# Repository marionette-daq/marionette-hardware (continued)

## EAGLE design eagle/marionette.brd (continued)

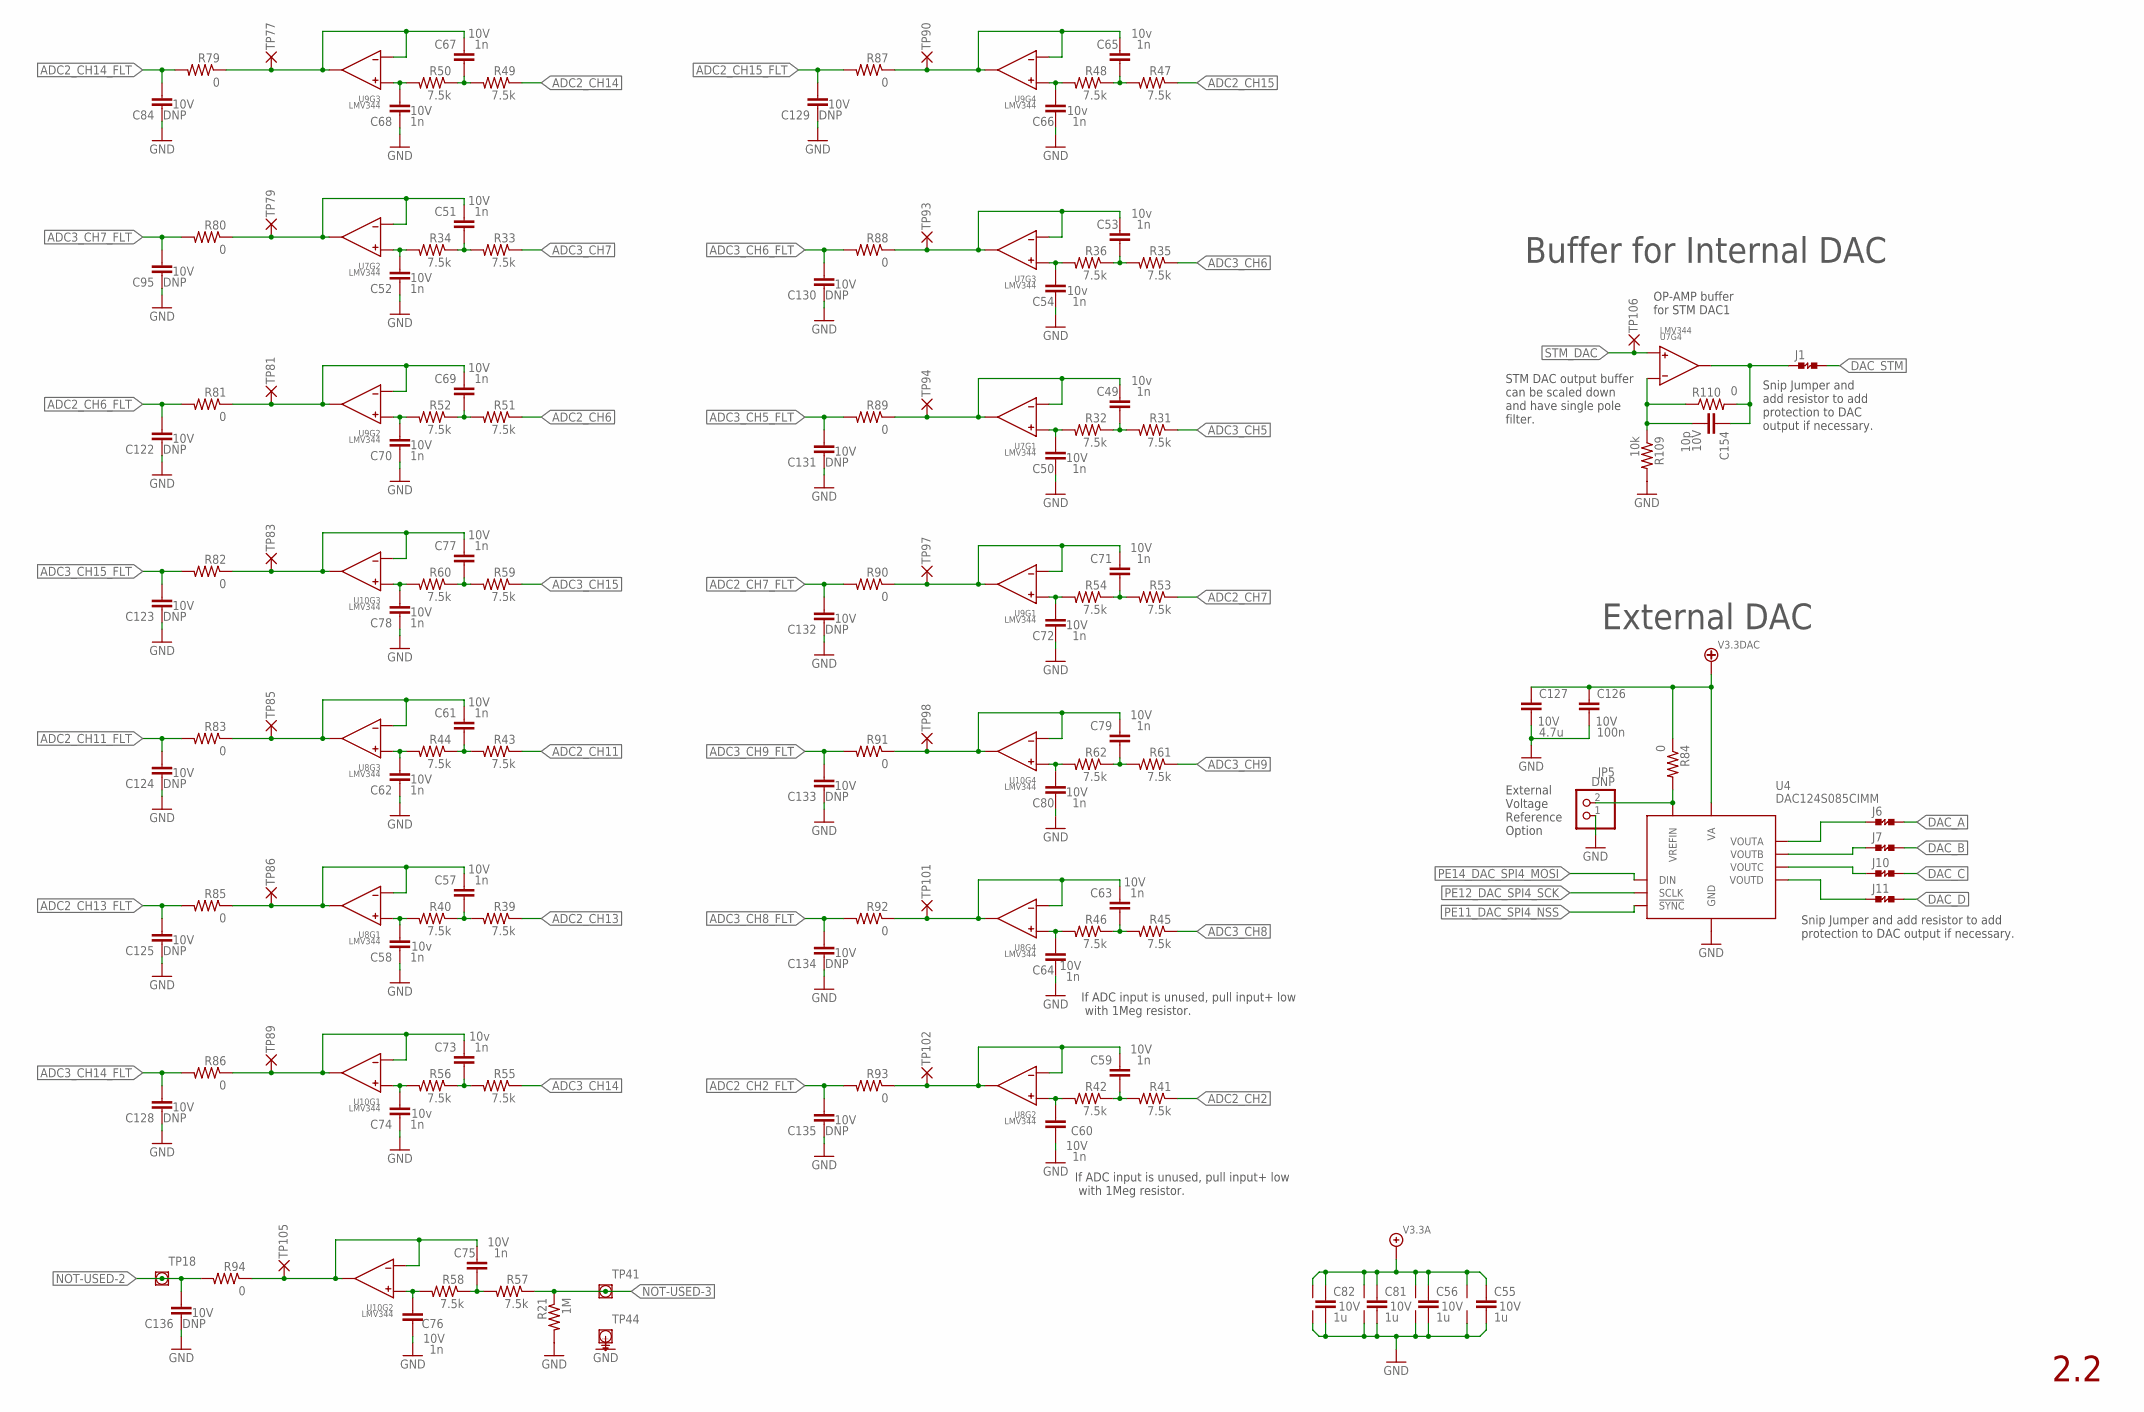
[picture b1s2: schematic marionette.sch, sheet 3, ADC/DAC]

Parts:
C49, C50, C51, C52, C53, C54, C57, C58, C59, C60, C61, C62, C63, C64, C65, C66, C67, C68, C69, C70, C71, C72, C73, C74, C75, C76, C77, C78, C79, C80: 1n; .0402-B
C55, C56, C81, C82: 1u; .0402-B
C84, C95, C122, C123, C124, C125, C128, C129, C130, C131, C132, C133, C134, C135, C136: DNP; .0402-B
C126: 100n; .0402-B
C127: 4.7u; .0805-B
C154: 10p; .0402-B
J1, J6, J7, J10, J11: JUMPER-SHORTED-CUTTABLE-E0402-0.3MM
JP5: DNP; 1X02
R21: 1M; .0402-B
R31, R32, R33, R34, R35, R36, R39, R40, R41, R42, R43, R44, R45, R46, R47, R48, R49, R50, R51, R52, R53, R54, R55, R56, R57, R58, R59, R60, R61, R62: 7.5k; .0402-B
R79, R80, R81, R82, R83, R84, R85, R86, R87, R88, R89, R90, R91, R92, R93, R94, R110: 0; .0402-B
R109: 10k; .0402-B
TP18, TP41: PAD+VIA_0.6MM
TP44: PAD+VIA_GND_0.6MM; PAD+GND_VIA_0.6MM
TP77, TP79, TP81, TP83, TP85, TP86, TP89, TP90, TP93, TP94, TP97, TP98, TP101, TP102, TP105, TP106: PAD+X-0.7-NO_CREAM+SILK; PAD-ROUND-0.7-NOCREAM+SILK
U4: DAC124S085CIMM; 10-TFSOP
U7, U8, U9, U10: LMV344; SOIC-14

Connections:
ADC1/2/3_CH2_OUT: C59.1, R93.1, TP102.PAD, U8.6 (-V), U8.7 (OUT)
ADC1/2/3_CH11_OUT: C61.1, R83.1, TP85.PAD, U8.8 (OUT), U8.9 (-V)
ADC1/2/3_CH13_OUT: C57.1, R85.1, TP86.PAD, U8.1 (OUT), U8.2 (-V)
ADC1/2/3_IN2+: C60.1, R42.2, U8.5 (+V)
ADC1/2/3_IN2_FILT: C59.2, R41.2, R42.1
ADC1/2/3_IN11+: C62.1, R44.2, U8.10 (+V)
ADC1/2/3_IN11_FILT: C61.2, R43.2, R44.1
ADC1/2/3_IN13+: C58.1, R40.2, U8.3 (+V)
ADC1/2/3_IN13_FILT: C57.2, R39.2, R40.1
ADC1/2_CH6_OUT: C69.1, R81.1, TP81.PAD, U9.6 (-V), U9.7 (OUT)
ADC1/2_CH7_OUT: C71.1, R90.1, TP97.PAD, U9.1 (OUT), U9.2 (-V)
ADC1/2_CH14_OUT: C67.1, R79.1, TP77.PAD, U9.8 (OUT), U9.9 (-V)
ADC1/2_CH15_OUT: C65.1, R87.1, TP90.PAD, U9.13 (-V), U9.14 (OUT)
ADC1/2_IN6+: C70.1, R52.2, U9.5 (+V)
ADC1/2_IN6_FILT: C69.2, R51.2, R52.1
ADC1/2_IN7+: C72.1, R54.2, U9.3 (+V)
ADC1/2_IN7_FILT: C71.2, R53.2, R54.1
ADC1/2_IN14+: C68.1, R50.2, U9.10 (+V)
ADC1/2_IN14_FILT: C67.2, R49.2, R50.1
ADC1/2_IN15+: C66.1, R48.2, U9.12 (+V)
ADC1/2_IN15_FILT: C65.2, R47.2, R48.1
ADC2_CH2: R41.1; also elsewhere on the board
ADC2_CH2_FLT: C135.1, R93.2; also elsewhere on the board
ADC2_CH6: R51.1; also elsewhere on the board
ADC2_CH6_FLT: C122.1, R81.2; also elsewhere on the board
ADC2_CH7: R53.1; also elsewhere on the board
ADC2_CH7_FLT: C132.1, R90.2; also elsewhere on the board
ADC2_CH11: R43.1; also elsewhere on the board
ADC2_CH11_FLT: C124.1, R83.2; also elsewhere on the board
ADC2_CH13: R39.1; also elsewhere on the board
ADC2_CH13_FLT: C125.1, R85.2; also elsewhere on the board
ADC2_CH14: R49.1; also elsewhere on the board
ADC2_CH14_FLT: C84.1, R79.2; also elsewhere on the board
ADC2_CH15: R47.1; also elsewhere on the board
ADC2_CH15_FLT: C129.1, R87.2; also elsewhere on the board
ADC3_CH4_OUT: C75.1, R94.1, TP105.PAD, U10.6 (-V), U10.7 (OUT)
ADC3_CH5: R31.1; also elsewhere on the board
ADC3_CH5_FLT: C131.1, R89.2; also elsewhere on the board
ADC3_CH5_OUT: C49.1, R89.1, TP94.PAD, U7.1 (OUT), U7.2 (-V)
ADC3_CH6: R35.1; also elsewhere on the board
ADC3_CH6_FLT: C130.1, R88.2; also elsewhere on the board
ADC3_CH6_OUT: C53.1, R88.1, TP93.PAD, U7.8 (OUT), U7.9 (-V)
ADC3_CH7: R33.1; also elsewhere on the board
ADC3_CH7_FLT: C95.1, R80.2; also elsewhere on the board
ADC3_CH7_OUT: C51.1, R80.1, TP79.PAD, U7.6 (-V), U7.7 (OUT)
ADC3_CH8: R45.1; also elsewhere on the board
ADC3_CH8_FLT: C134.1, R92.2; also elsewhere on the board
ADC3_CH8_OUT: C63.1, R92.1, TP101.PAD, U8.13 (-V), U8.14 (OUT)
ADC3_CH9: R61.1; also elsewhere on the board
ADC3_CH9_FLT: C133.1, R91.2; also elsewhere on the board
ADC3_CH14: R55.1; also elsewhere on the board
ADC3_CH14_FLT: C128.1, R86.2; also elsewhere on the board
ADC3_CH14_OUT: C73.1, R86.1, TP89.PAD, U10.1 (OUT), U10.2 (-V)
ADC3_CH15: R59.1; also elsewhere on the board
ADC3_CH15_FLT: C123.1, R82.2; also elsewhere on the board
ADC3_CH15_OUT: C77.1, R82.1, TP83.PAD, U10.8 (OUT), U10.9 (-V)
ADC3_IN4+: C76.1, R58.2, U10.5 (+V)
ADC3_IN4_FILT: C75.2, R57.2, R58.1
ADC3_IN5+: C50.1, R32.2, U7.3 (+V)
ADC3_IN5_FILT: C49.2, R31.2, R32.1
ADC3_IN6+: C54.1, R36.2, U7.10 (+V)
ADC3_IN6_FILT: C53.2, R35.2, R36.1
ADC3_IN7+: C52.1, R34.2, U7.5 (+V)
ADC3_IN7_FILT: C51.2, R33.2, R34.1
ADC3_IN8+: C64.1, R46.2, U8.12 (+V)
ADC3_IN8_FILT: C63.2, R45.2, R46.1
ADC3_IN9+: C80.1, R62.2, U10.12 (+V)
ADC3_IN9_FILT: C79.2, R61.2, R62.1
ADC3_IN9_OUT: C79.1, R91.1, TP98.PAD, U10.13 (-V), U10.14 (OUT)
ADC3_IN14+: C74.1, R56.2, U10.3 (+V)
ADC3_IN14_FILT: C73.2, R55.2, R56.1
ADC3_IN15+: C78.1, R60.2, U10.10 (+V)
ADC3_IN15_FILT: C77.2, R59.2, R60.1
DAC124_VREFIN: JP5.2, R84.2, U4.7 (VREFIN)
DAC_A: J6.2; also elsewhere on the board
DAC_A_JUMPERED: J6.1, U4.2 (VOUTA)
DAC_B: J7.2; also elsewhere on the board
DAC_B_JUMPERED: J7.1, U4.3 (VOUTB)
DAC_C: J10.2; also elsewhere on the board
DAC_C_JUMPERED: J10.1, U4.4 (VOUTC)
DAC_D: J11.2; also elsewhere on the board
DAC_D_JUMPERED: J11.1, U4.5 (VOUTD)
DAC_STM: J1.2; also elsewhere on the board
GND: C50.2, C52.2, C54.2, C55.2, C56.2, C58.2, C60.2, C62.2, C64.2, C66.2, C68.2, C70.2, C72.2, C74.2, C76.2, C78.2, C80.2, C81.2, C82.2, C84.2, C95.2, C122.2, C123.2, C124.2, C125.2, C126.2, C127.2, C128.2, C129.2, C130.2, C131.2, C132.2, C133.2, C134.2, C135.2, C136.2, JP5.1, R21.2, R109.2, TP44.TP, U4.6 (GND), U7.11 (GND), U8.11 (GND), U9.11 (GND), U10.11 (GND); also elsewhere on the board
NOT-USED-2: C136.1, R94.2, TP18.TP
NOT-USED-3: R21.1, R57.1, TP41.TP
PE11_DAC_SPI4_NSS: U4.9 (!SYNC!); also elsewhere on the board
PE12_DAC_SPI4_SCK: U4.10 (SCLK); also elsewhere on the board
PE14_DAC_SPI4_MOSI: U4.8 (DIN); also elsewhere on the board
STM_DAC: TP106.PAD, U7.12 (+V); also elsewhere on the board
STM_DAC-: C154.2, R109.1, R110.1, U7.13 (-V)
STM_DAC_OUT: C154.1, J1.1, R110.2, U7.14 (OUT)
V3.3A: C55.1, C56.1, C81.1, C82.1, U7.4 (VCC), U8.4 (VCC), U9.4 (VCC), U10.4 (VCC); also elsewhere on the board
V3.3DAC: C126.1, C127.1, R84.1, U4.1 (VA); also elsewhere on the board

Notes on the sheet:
OP-AMP buffer for STM DAC1
External DAC
Buffer for Internal DAC
External Voltage Reference Option
STM DAC output buffer can be scaled down and have single pole filter.
If ADC input is unused, pull input+ low with 1Meg resistor.
Snip Jumper and add resistor to add protection to DAC output if necessary.
Snip Jumper and add resistor to add protection to DAC output if necessary.

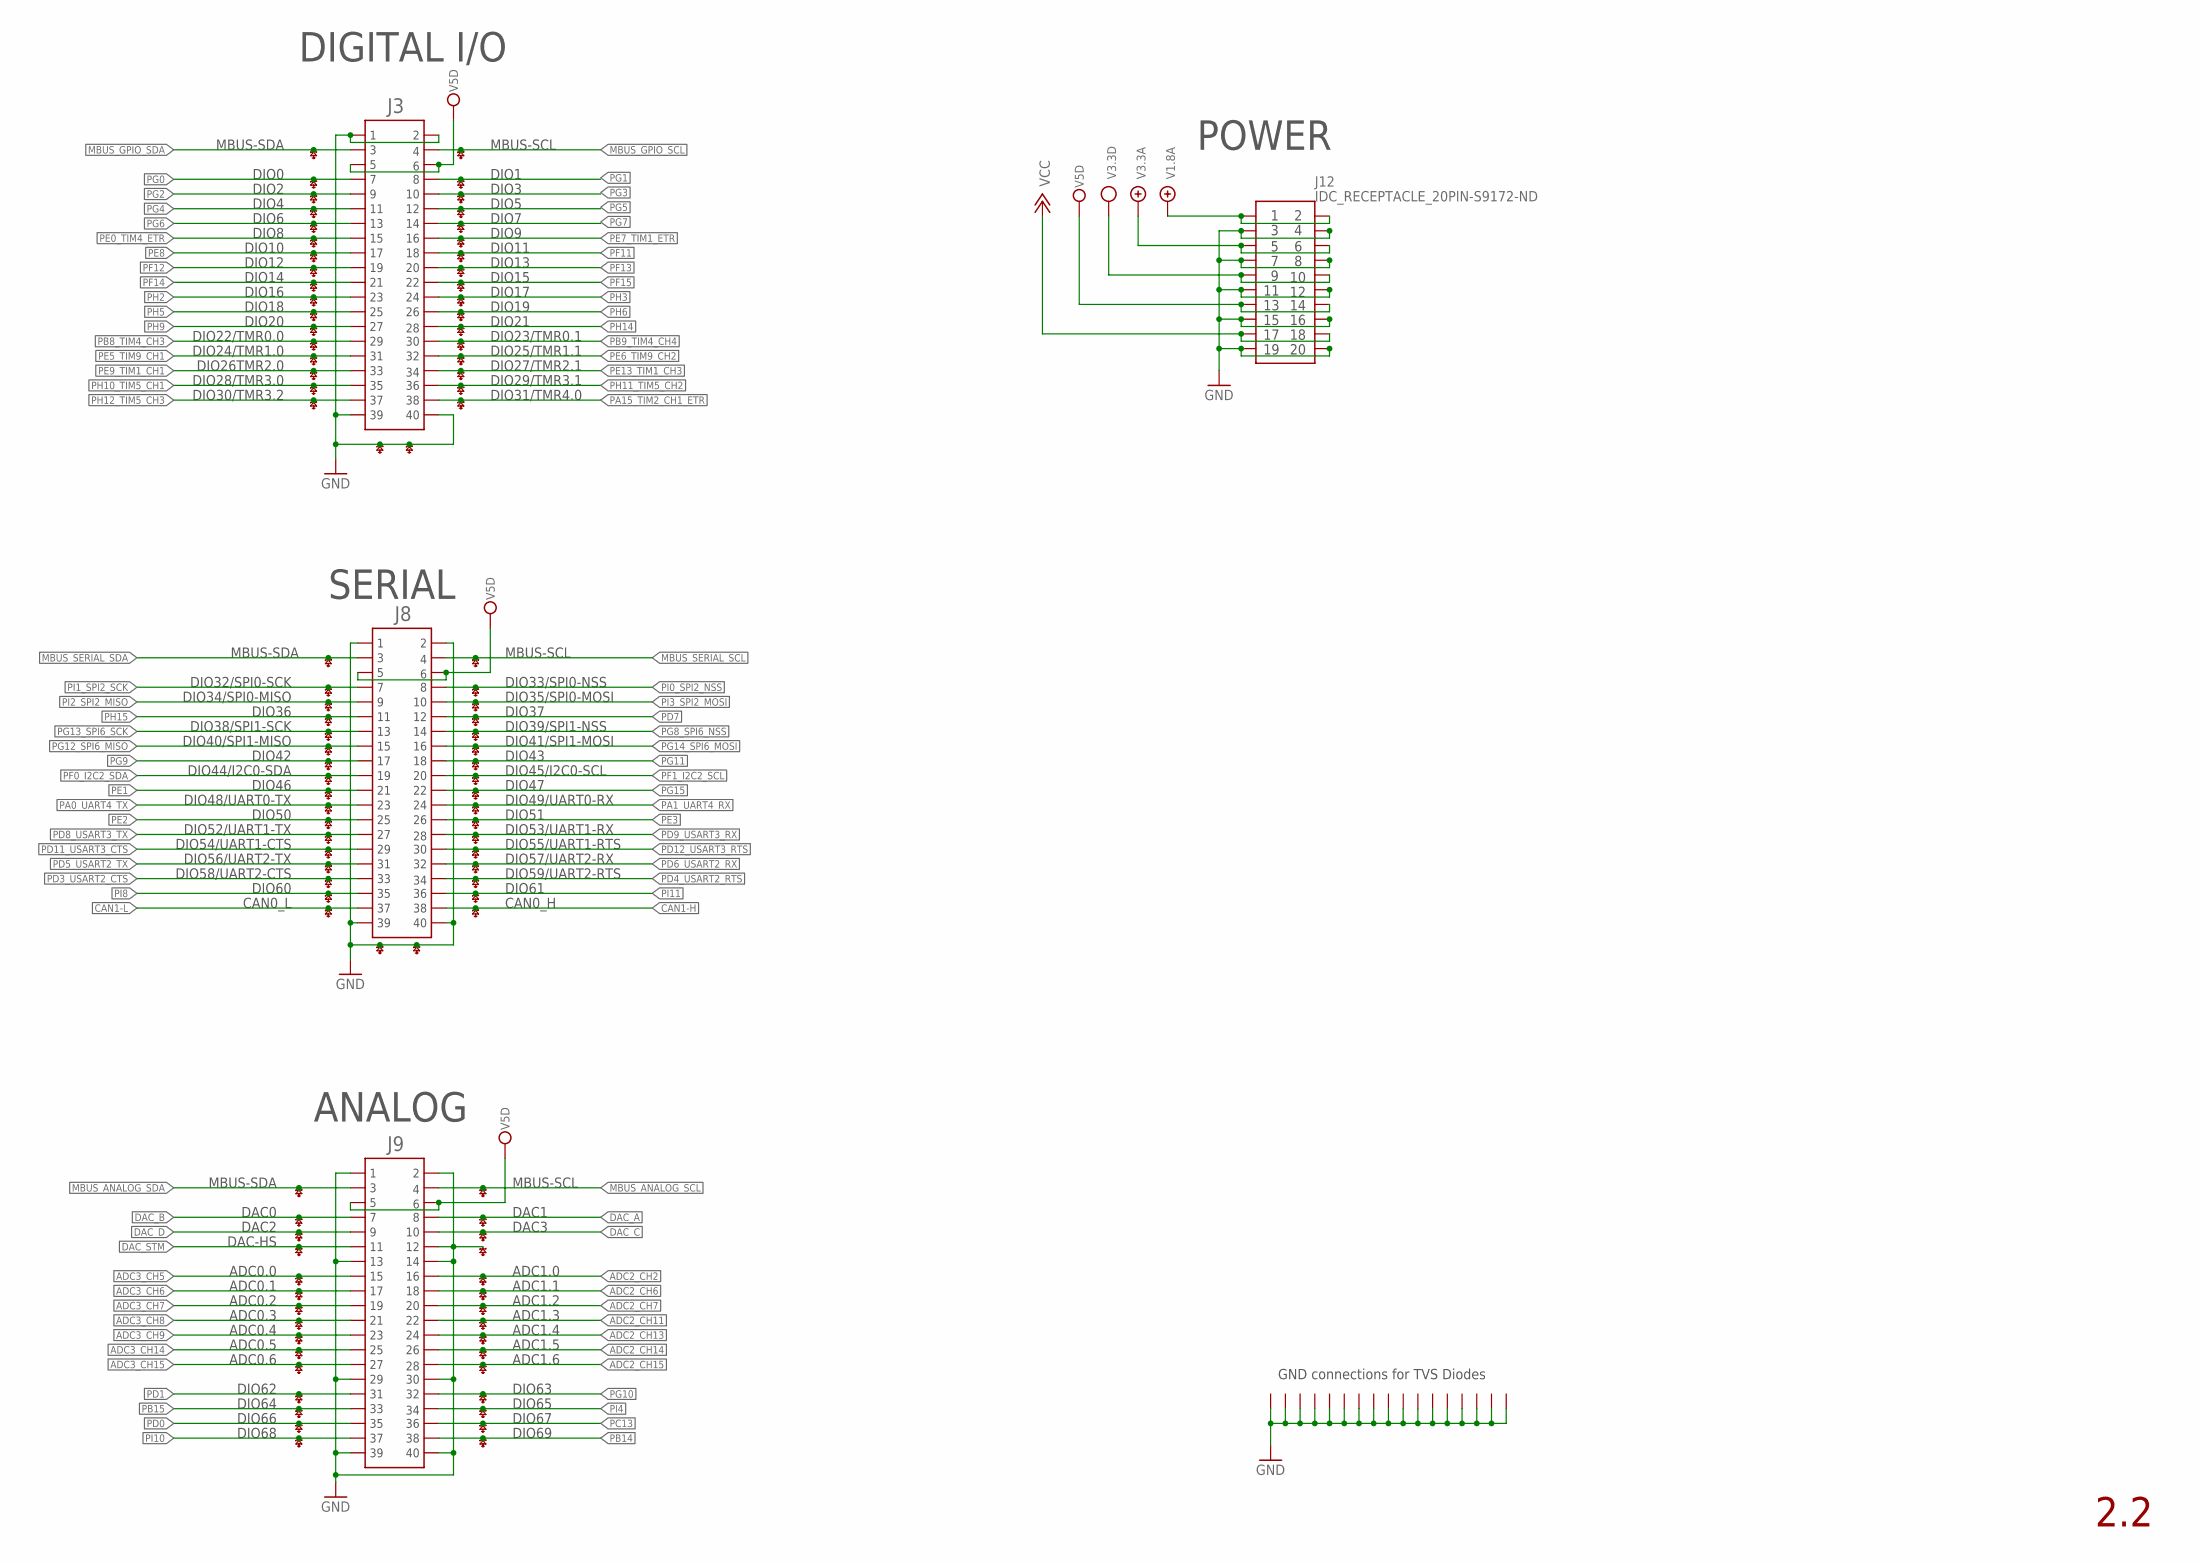
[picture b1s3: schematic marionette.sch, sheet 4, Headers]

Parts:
D1, D2, D4, D5, D6, D7, D8, D9, D10, D11, D12, D13, D14, D15, D16, D17, D18: ESD8006-ESD8006; UDFN-8-3.3X1.0_6MIL
J3, J8, J9: IDC_RECEPTACLE_2X20-S9175-ND; IDC_RECEPTACLES
J12: IDC_RECEPTACLE_20PIN-S9172-ND; IDC_RECEPTACLES_20PIN

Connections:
ADC2_CH2: D1.5 (CATHODE), J9.16; also elsewhere on the board
ADC2_CH6: D1.2 (CATHODE), J9.18; also elsewhere on the board
ADC2_CH7: D5.7 (CATHODE), J9.20; also elsewhere on the board
ADC2_CH11: D5.4 (CATHODE), J9.22; also elsewhere on the board
ADC2_CH13: D5.2 (CATHODE), J9.24; also elsewhere on the board
ADC2_CH14: D6.7 (CATHODE), J9.26; also elsewhere on the board
ADC2_CH15: D6.4 (CATHODE), J9.28; also elsewhere on the board
ADC3_CH5: D1.4 (CATHODE), J9.15; also elsewhere on the board
ADC3_CH6: D1.1 (CATHODE), J9.17; also elsewhere on the board
ADC3_CH7: D5.8 (CATHODE), J9.19; also elsewhere on the board
ADC3_CH8: D5.5 (CATHODE), J9.21; also elsewhere on the board
ADC3_CH9: D5.1 (CATHODE), J9.23; also elsewhere on the board
ADC3_CH14: D6.8 (CATHODE), J9.25; also elsewhere on the board
ADC3_CH15: D6.5 (CATHODE), J9.27; also elsewhere on the board
CAN1-H: D12.4 (CATHODE), J8.38; also elsewhere on the board
CAN1-L: D12.5 (CATHODE), J8.37; also elsewhere on the board
DAC_A: D2.5 (CATHODE), J9.8; also elsewhere on the board
DAC_B: D2.4 (CATHODE), J9.7; also elsewhere on the board
DAC_C: D2.2 (CATHODE), J9.10; also elsewhere on the board
DAC_D: D2.1 (CATHODE), J9.9; also elsewhere on the board
DAC_STM: D1.8 (CATHODE), J9.11; also elsewhere on the board
GND: D1.3 (PIN), D1.6 (PIN), D1.7 (CATHODE), D1.9 (PIN), D1.10 (PIN), D2.3 (PIN), D2.6 (PIN), D2.9 (PIN), D2.10 (PIN), D4.3 (PIN), D4.6 (PIN), D4.9 (PIN), D4.10 (PIN), D5.3 (PIN), D5.6 (PIN), D5.9 (PIN), D5.10 (PIN), D6.3 (PIN), D6.6 (PIN), D6.9 (PIN), D6.10 (PIN), D7.3 (PIN), D7.6 (PIN), D7.9 (PIN), D7.10 (PIN), D8.3 (PIN), D8.6 (PIN), D8.9 (PIN), D8.10 (PIN), D9.3 (PIN), D9.6 (PIN), D9.9 (PIN), D9.10 (PIN), D10.3 (PIN), D10.6 (PIN), D10.9 (PIN), D10.10 (PIN), D11.3 (PIN), D11.6 (PIN), D11.9 (PIN), D11.10 (PIN), D12.1 (CATHODE), D12.2 (CATHODE), D12.3 (PIN), D12.6 (PIN), D12.9 (PIN), D12.10 (PIN), D13.1 (CATHODE), D13.2 (CATHODE), D13.3 (PIN), D13.6 (PIN), D13.9 (PIN), D13.10 (PIN), D14.3 (PIN), D14.6 (PIN), D14.9 (PIN), D14.10 (PIN), D15.3 (PIN), D15.6 (PIN), D15.9 (PIN), D15.10 (PIN), D16.3 (PIN), D16.6 (PIN), D16.9 (PIN), D16.10 (PIN), D17.3 (PIN), D17.6 (PIN), D17.9 (PIN), D17.10 (PIN), D18.3 (PIN), D18.6 (PIN), D18.9 (PIN), D18.10 (PIN), J3.1, J3.2, J3.39, J3.40, J8.1, J8.2, J8.39, J8.40, J9.1, J9.2, J9.12, J9.13, J9.14, J9.29, J9.30, J9.39, J9.40, J12.3, J12.4, J12.7, J12.8, J12.11, J12.12, J12.15, J12.16, J12.19, J12.20; also elsewhere on the board
MBUS_ANALOG_SCL: D2.7 (CATHODE), J9.4; also elsewhere on the board
MBUS_ANALOG_SDA: D2.8 (CATHODE), J9.3; also elsewhere on the board
MBUS_GPIO_SCL: D18.8 (CATHODE), J3.4; also elsewhere on the board
MBUS_GPIO_SDA: D18.7 (CATHODE), J3.3; also elsewhere on the board
MBUS_SERIAL_SCL: D4.7 (CATHODE), J8.4; also elsewhere on the board
MBUS_SERIAL_SDA: D4.8 (CATHODE), J8.3; also elsewhere on the board
PA0_UART4_TX: D9.8 (CATHODE), J8.23; also elsewhere on the board
PA1_UART4_RX: D9.7 (CATHODE), J8.24; also elsewhere on the board
PA15_TIM2_CH1_ETR: D13.4 (CATHODE), J3.38; also elsewhere on the board
PB8_TIM4_CH3: D14.8 (CATHODE), J3.29; also elsewhere on the board
PB9_TIM4_CH4: D14.7 (CATHODE), J3.30; also elsewhere on the board
PB14: D7.2 (CATHODE), J9.38; also elsewhere on the board
PB15: D7.8 (CATHODE), J9.33; also elsewhere on the board
PC13: D7.4 (CATHODE), J9.36; also elsewhere on the board
PD0: D7.5 (CATHODE), J9.35; also elsewhere on the board
PD1: D6.1 (CATHODE), J9.31; also elsewhere on the board
PD3_USART2_CTS: D11.1 (CATHODE), J8.33; also elsewhere on the board
PD4_USART2_RTS: D11.2 (CATHODE), J8.34; also elsewhere on the board
PD5_USART2_TX: D11.5 (CATHODE), J8.31; also elsewhere on the board
PD6_USART2_RX: D11.4 (CATHODE), J8.32; also elsewhere on the board
PD7: D8.7 (CATHODE), J8.12; also elsewhere on the board
PD8_USART3_TX: D9.1 (CATHODE), J8.27; also elsewhere on the board
PD9_USART3_RX: D9.2 (CATHODE), J8.28; also elsewhere on the board
PD11_USART3_CTS: D11.8 (CATHODE), J8.29; also elsewhere on the board
PD12_USART3_RTS: D11.7 (CATHODE), J8.30; also elsewhere on the board
PE0_TIM4_ETR: D17.1 (CATHODE), J3.15; also elsewhere on the board
PE1: D10.1 (CATHODE), J8.21; also elsewhere on the board
PE2: D9.5 (CATHODE), J8.25; also elsewhere on the board
PE3: D9.4 (CATHODE), J8.26; also elsewhere on the board
PE5_TIM9_CH1: D14.5 (CATHODE), J3.31; also elsewhere on the board
PE6_TIM9_CH2: D14.4 (CATHODE), J3.32; also elsewhere on the board
PE7_TIM1_ETR: D17.2 (CATHODE), J3.16; also elsewhere on the board
PE8: D16.8 (CATHODE), J3.17; also elsewhere on the board
PE9_TIM1_CH1: D14.1 (CATHODE), J3.33; also elsewhere on the board
PE13_TIM1_CH3: D14.2 (CATHODE), J3.34; also elsewhere on the board
PF0_I2C2_SDA: D10.5 (CATHODE), J8.19; also elsewhere on the board
PF1_I2C2_SCL: D10.4 (CATHODE), J8.20; also elsewhere on the board
PF11: D16.7 (CATHODE), J3.18; also elsewhere on the board
PF12: D16.5 (CATHODE), J3.19; also elsewhere on the board
PF13: D16.4 (CATHODE), J3.20; also elsewhere on the board
PF14: D16.1 (CATHODE), J3.21; also elsewhere on the board
PF15: D16.2 (CATHODE), J3.22; also elsewhere on the board
PG0: D18.5 (CATHODE), J3.7; also elsewhere on the board
PG1: D18.4 (CATHODE), J3.8; also elsewhere on the board
PG2: D18.2 (CATHODE), J3.9; also elsewhere on the board
PG3: D18.1 (CATHODE), J3.10; also elsewhere on the board
PG4: D17.8 (CATHODE), J3.11; also elsewhere on the board
PG5: D17.7 (CATHODE), J3.12; also elsewhere on the board
PG6: D17.5 (CATHODE), J3.13; also elsewhere on the board
PG7: D17.4 (CATHODE), J3.14; also elsewhere on the board
PG8_SPI6_NSS: D8.4 (CATHODE), J8.14; also elsewhere on the board
PG9: D10.8 (CATHODE), J8.17; also elsewhere on the board
PG10: D6.2 (CATHODE), J9.32; also elsewhere on the board
PG11: D10.7 (CATHODE), J8.18; also elsewhere on the board
PG12_SPI6_MISO: D8.1 (CATHODE), J8.15; also elsewhere on the board
PG13_SPI6_SCK: D8.5 (CATHODE), J8.13; also elsewhere on the board
PG14_SPI6_MOSI: D8.2 (CATHODE), J8.16; also elsewhere on the board
PG15: D10.2 (CATHODE), J8.22; also elsewhere on the board
PH2: D15.8 (CATHODE), J3.23; also elsewhere on the board
PH3: D15.7 (CATHODE), J3.24; also elsewhere on the board
PH5: D15.5 (CATHODE), J3.25; also elsewhere on the board
PH6: D15.4 (CATHODE), J3.26; also elsewhere on the board
PH9: D15.1 (CATHODE), J3.27; also elsewhere on the board
PH10_TIM5_CH1: D13.8 (CATHODE), J3.35; also elsewhere on the board
PH11_TIM5_CH2: D13.7 (CATHODE), J3.36; also elsewhere on the board
PH12_TIM5_CH3: D13.5 (CATHODE), J3.37; also elsewhere on the board
PH14: D15.2 (CATHODE), J3.28; also elsewhere on the board
PH15: D8.8 (CATHODE), J8.11; also elsewhere on the board
PI0_SPI2_NSS: D4.5 (CATHODE), J8.8; also elsewhere on the board
PI1_SPI2_SCK: D4.4 (CATHODE), J8.7; also elsewhere on the board
PI2_SPI2_MISO: D4.1 (CATHODE), J8.9; also elsewhere on the board
PI3_SPI2_MOSI: D4.2 (CATHODE), J8.10; also elsewhere on the board
PI4: D7.7 (CATHODE), J9.34; also elsewhere on the board
PI8: D12.8 (CATHODE), J8.35; also elsewhere on the board
PI10: D7.1 (CATHODE), J9.37; also elsewhere on the board
PI11: D12.7 (CATHODE), J8.36; also elsewhere on the board
V1.8A: J12.1, J12.2; also elsewhere on the board
V3.3A: J12.5, J12.6; also elsewhere on the board
V3.3D: J12.9, J12.10; also elsewhere on the board
V5D: J3.5, J3.6, J8.5, J8.6, J9.5, J9.6, J12.13, J12.14; also elsewhere on the board
VCC: J12.17, J12.18; also elsewhere on the board

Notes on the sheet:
POWER
GND connections for TVS Diodes
DIO22/TMR0.0
DIO23/TMR0.1
DIO24/TMR1.0
DIO25/TMR1.1
DIO26TMR2.0
DIO27/TMR2.1
DIO28/TMR3.0
DIO29/TMR3.1
DIO30/TMR3.2
DIO31/TMR4.0
DAC0
DAC1
DAC2
DAC3
DAC-HS
ADC1.0
ADC1.1
ADC1.2
ADC1.3
ADC1.4
ADC1.5
ADC0.0
ADC0.1
ADC0.2
ADC0.3
ADC0.4
ADC0.5
DIO32/SPI0-SCK
DIO34/SPI0-MISO
DIO35/SPI0-MOSI
DIO33/SPI0-NSS
DIO38/SPI1-SCK
DIO40/SPI1-MISO
DIO41/SPI1-MOSI
DIO39/SPI1-NSS
DIO44/I2C0-SDA
DIO45/I2C0-SCL
CAN0_L

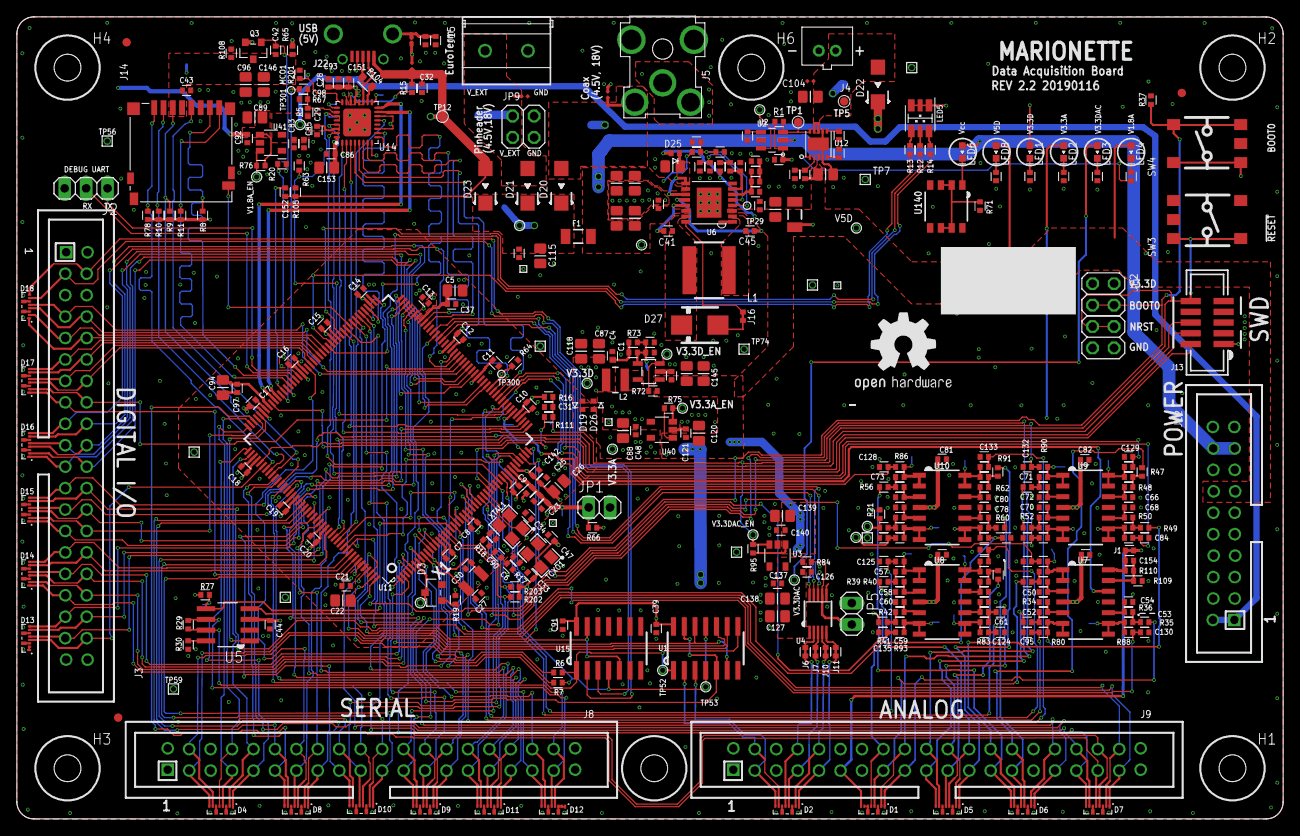
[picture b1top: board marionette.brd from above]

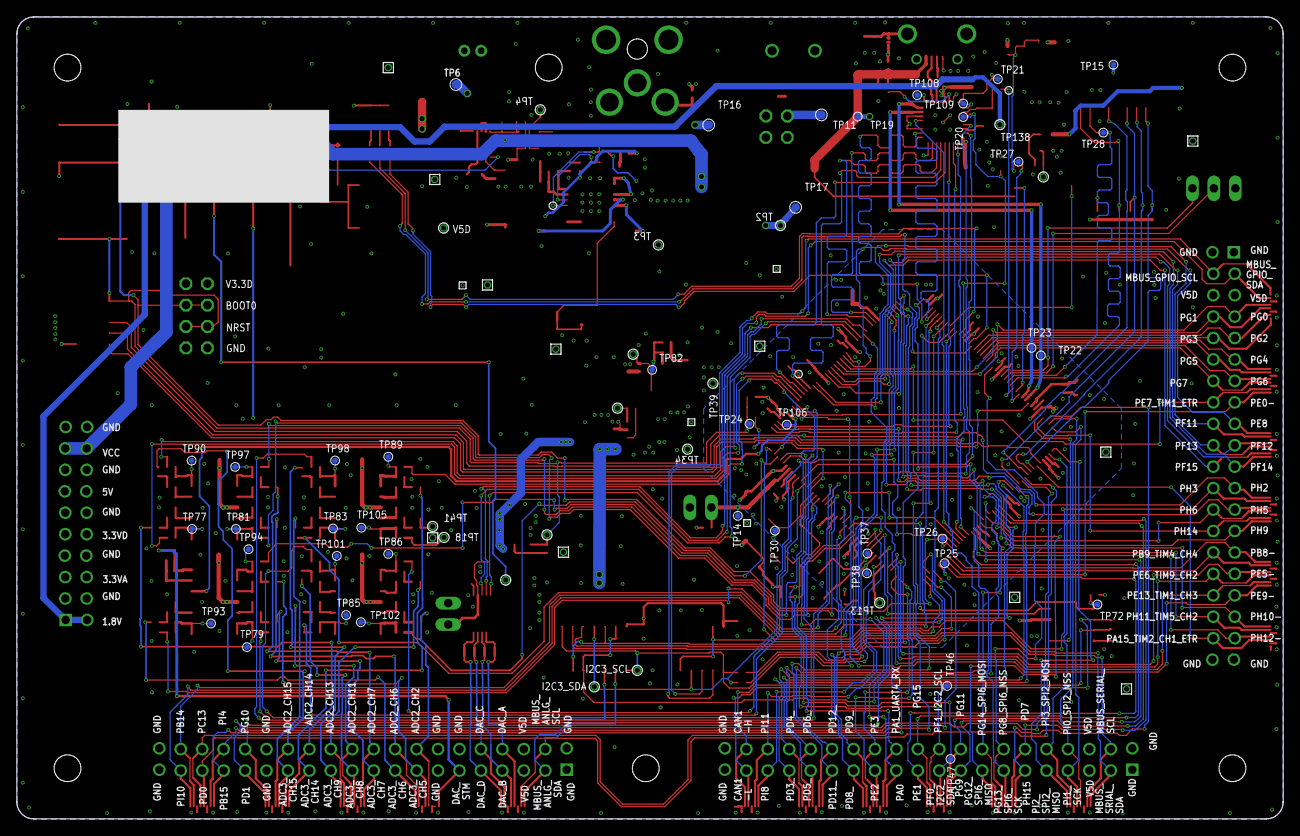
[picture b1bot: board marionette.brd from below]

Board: 4 copper layers, 150.0 x 95.0 mm, 437 parts (50 on the bottom side), 289 nets.

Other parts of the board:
U$1: OSHW1
